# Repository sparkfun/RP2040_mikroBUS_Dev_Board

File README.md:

SparkFun RP2040 mikroBUS™ Development Board
========================================

[*SparkFun RP2040 mikroBUS™ Development Board (DEV-18721)*](https://www.sparkfun.com/products/18721)

The SparkFun RP2040 mikroBUS™ development board is a low-cost, high performance board with flexible digital interfaces featuring the Raspberry Pi Foundation's RP2040 microcontroller. Besides the Thing Plus or *Feather* footprint (with 18 GPIO pins), the board also includes an SD card slot, 16MB (128Mbit) flash memory, a JST single cell battery connector (with a charging circuit and fuel gauge sensor), an addressable WS2812 RGB LED, JTAG PTH pins, a mikroBUS™ socket, and our signature Qwiic connector.

_The RP2040 is supported with both C/C++ and MicroPython cross-platform development environments, including easy access to runtime debugging. It has UF2 boot and floating-point routines baked into the chip. While the chip has a large amount of internal RAM, the board includes an additional 16MB of external QSPI flash memory to store program code._

_The [mikroBUS™ standard](https://www.mikroe.com/mikrobus) was developed by [MikroElektronika](https://www.mikroe.com/). Similar to our [Qwiic](https://www.sparkfun.com/qwiic) and [MicroMod](https://www.sparkfun.com/micromod) interfaces, mikroBUS™ provides a standardized connection for add-on [Click boards™](https://www.mikroe.com/click-boards) to be hooked up to a microcontroller based development board._

Repository Contents
-------------------

* **/Documentation** - Data sheets, additional product information
* **/Hardware** - Eagle design files (.brd, .sch)

Documentation
--------------

* **[Hookup Guide](https://learn.sparkfun.com/tutorials/2004)** - SparkFun RP2040 mikroBUS™ Development Board
* **[Raspberry Pi RP2040 Datasheet](https://datasheets.raspberrypi.org/rp2040/rp2040_datasheet.pdf)** - Datasheet for the RP2040
* **[SparkFun Graphical Datasheets](https://github.com/sparkfun/Graphical_Datasheets)** - Graphical datasheets for various SparkFun products.

Product Versions
----------------
* [DEV-18721](https://www.sparkfun.com/products/18721) -  initial release

License Information
-------------------

This product is _**open source**_! 

Please review the LICENSE.md file for license information. 

If you have any questions or concerns on licensing, please contact technical support on our [SparkFun forums](https://forum.sparkfun.com/viewforum.php?f=152).

Distributed as-is; no warranty is given.

- Your friends at SparkFun.

_<COLLABORATION CREDIT>_

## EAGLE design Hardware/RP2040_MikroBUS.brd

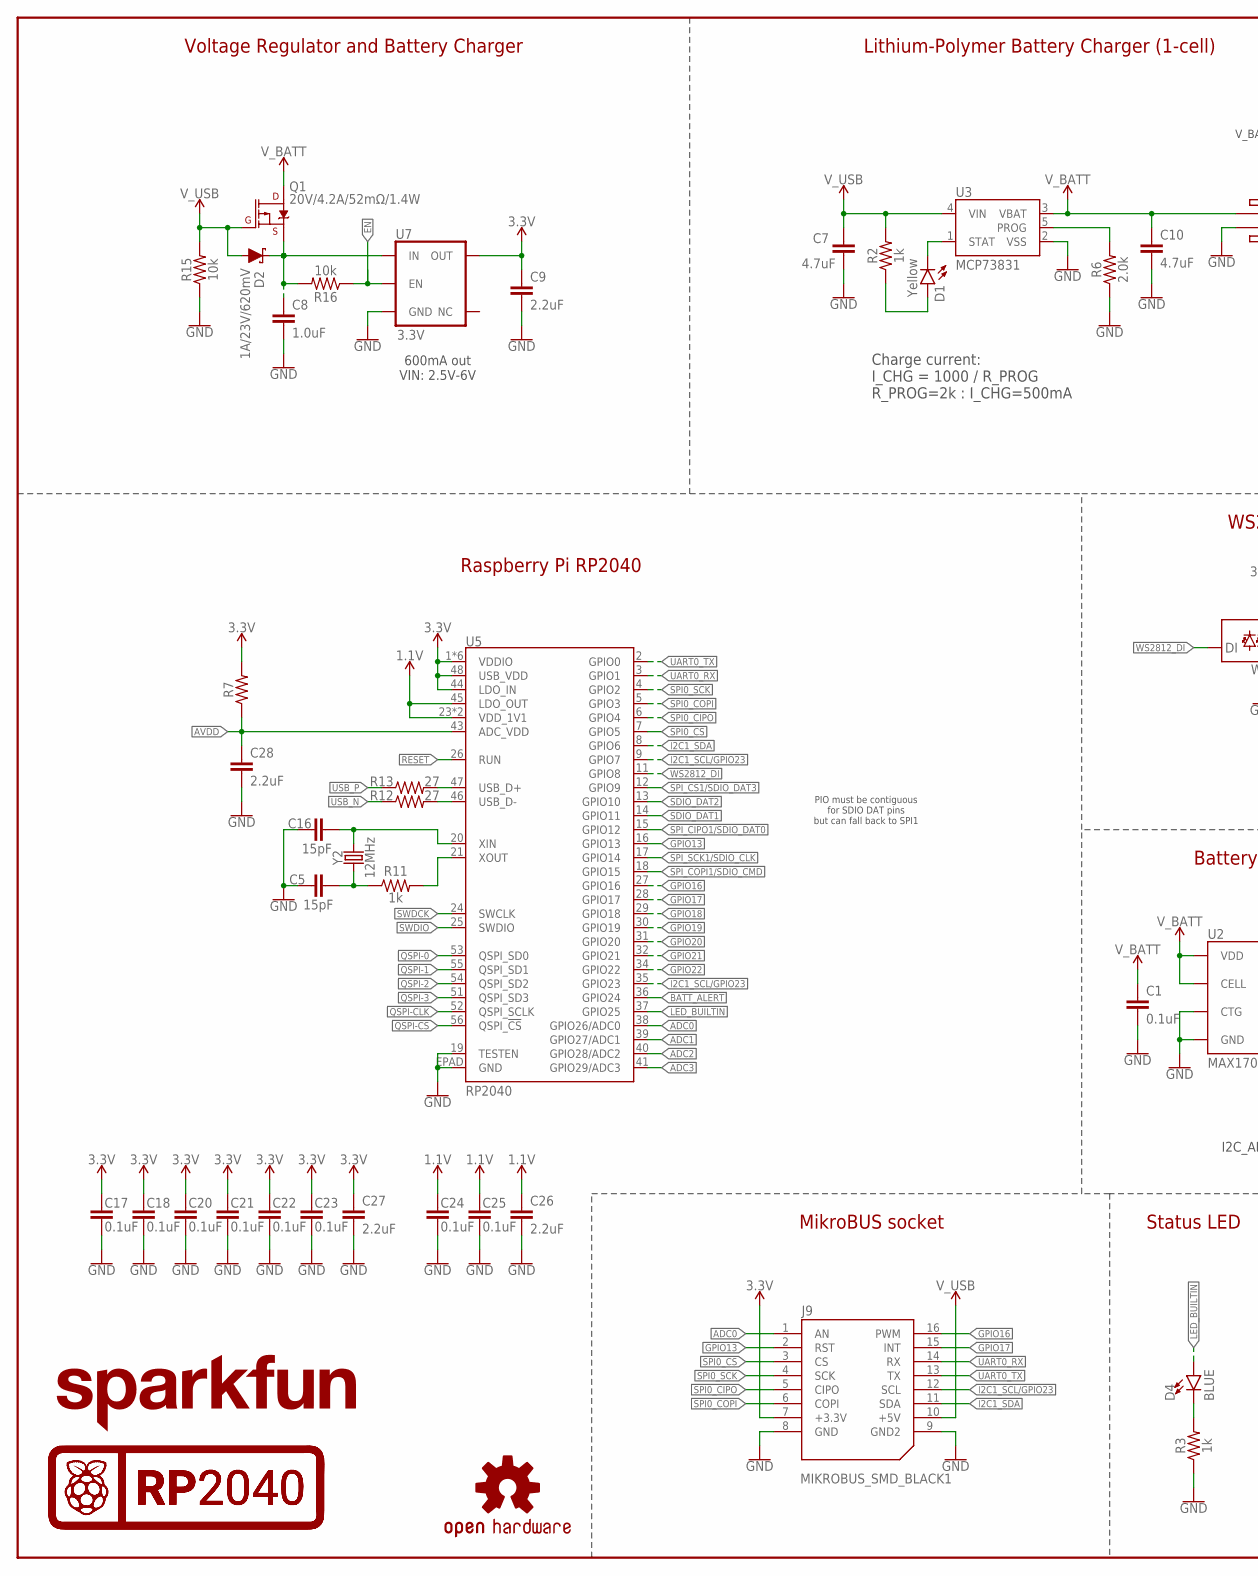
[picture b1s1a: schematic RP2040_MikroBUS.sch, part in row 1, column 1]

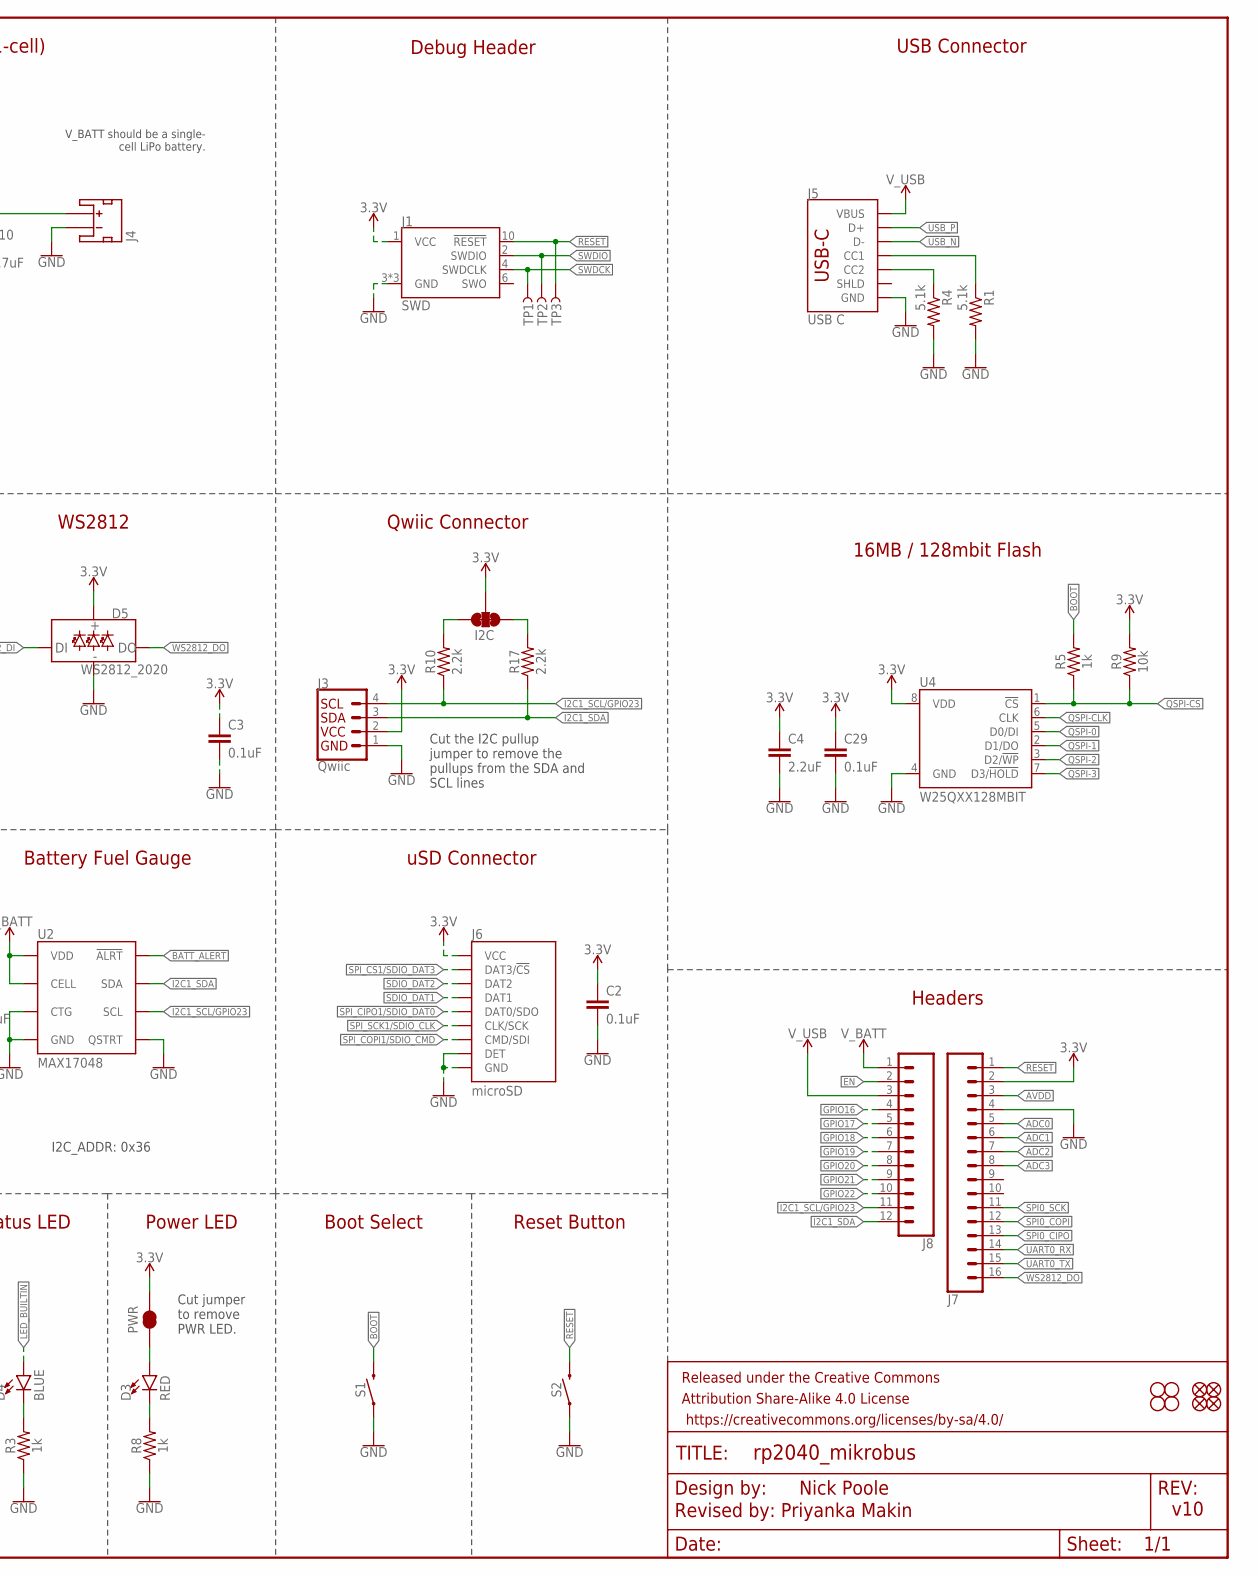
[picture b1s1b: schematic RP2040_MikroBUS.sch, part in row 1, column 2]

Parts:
C1, C2, C3, C17, C18, C20, C21, C22, C23, C24, C25, C29: 0.1uF; 0402-TIGHT
C4, C9, C26, C27, C28: 2.2uF; 0402-TIGHT
C5, C16: 15pF; 0402-TIGHT
C7, C10: 4.7uF; 0402-TIGHT
C8: 1.0uF; 0402-TIGHT
D1: Yellow; LED-0603
D2: 1A/23V/620mV; SOD-323
D3: RED; LED-0603
D4: BLUE; LED-0603
D5: WS2812_2020; WS2812-2020
FD1, FD2, FD3, FD4: FIDUCIALUFIDUCIAL; FIDUCIAL-MICRO
FRAME1: FRAME-LEDGER; CREATIVE_COMMONS
H1, H2, H3, H4: STAND-OFF
I2C: JUMPER-SMT_3_2-NC_TRACE_SILK; SMT-JUMPER_3_2-NC_TRACE_SILK
J1: SWD; 2X5-PTH-1.27MM
J3: Qwiic; JST04_1MM_RA
J4: JST_2MM_MALE; JST-2-SMD
J5: USB C; USB-C-16P-4LAYER-ISOLATED
J6: microSD; MICROSD-EXTERNALPIN
J7: CONN_161X16_NO_SILK; 1X16_NO_SILK
J8: CONN_12NO_SILK; 1X12_NO_SILK
J9: MIKROBUS_SMD_BLACK1; MIKROBUS_SMD_BLACK
LOGO1: OSHW-LOGOS; OSHW-LOGO-S
LOGO2: SFE_LOGO_NAME.1_INCH; SFE_LOGO_NAME_.1
PWR: JUMPER-SMT_2_NC_TRACE_SILK; SMT-JUMPER_2_NC_TRACE_SILK
Q1: 20V/4.2A/52mΩ/1.4W; SOT23-3
R1, R4: 5.1k; 0402-TIGHT
R2, R3, R5, R8, R11: 1k; 0402-TIGHT
R6: 2.0k; 0603
R7: 200OHM-0402T-1/16W-1%; 0402-TIGHT
R9, R15, R16: 10k; 0402-TIGHT
R10, R17: 2.2k; 0402-TIGHT
R12, R13: 27; 0402-TIGHT
S1, S2: MOMENTARY-SWITCH-SPST-SMD-5.2MM-TALL; TACTILE_SWITCH_SMD_5.2MM
TP1, TP2, TP3: TEST-POINT3X4; PAD.03X.04
U2: MAX17048; DFN-8
U3: MCP73831; SOT23-5
U4: W25QXX128MBIT; WSON-8-6X5-SKINNY_CENTERPAD
U5: RP2040; QFN-56
U7: 3.3V; SOT23-5
U$17, U$73: RASPI_RP2040_LOGO_10MM
Y2: 12MHz; CRYSTAL-SMD-2X2.5MM

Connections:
1.1V: C24.1, C25.1, C26.1, U5.23 (VDD_1V1), U5.45 (LDO_OUT), U5.50 (VDD_1V1)
3.3V: C2.1, C3.1, C4.1, C9.1, C17.1, C18.1, C20.1, C21.1, C22.1, C23.1, C27.1, C29.1, D5.VCC, I2C.2, J1.1 (VCC), J3.2, J6.4 (VCC), J7.2, J9.7 (+3.3V), PWR.2, R7.2, R9.2, U4.8 (VDD), U5.1 (VDDIO), U5.10 (VDDIO), U5.22 (VDDIO), U5.33 (VDDIO), U5.42 (VDDIO), U5.44 (LDO_IN), U5.48 (USB_VDD), U5.49 (VDDIO), U7.5 (OUT)
!BATT_ALERT!: U2.5 (!ALRT), U5.36 (GPIO24)
!BOOT!: R5.2, S1.3 (2)
!QSPI-CS!: R5.1, R9.1, U4.1 (!CS!), U5.56 (QSPI_!CS!)
!RESET!: J1.10 (!RESET), J7.1, S2.3 (2), TP3.1, U5.26 (RUN)
!SPI0_CS!: J9.3 (CS), U5.7 (GPIO5)
ADC0: J7.5, J9.1 (AN), U5.38 (GPIO26/ADC0)
ADC1: J7.6, U5.39 (GPIO27/ADC1)
ADC2: J7.7, U5.40 (GPIO28/ADC2)
ADC3: J7.8, U5.41 (GPIO29/ADC3)
AVDD: C28.1, J7.3, R7.1, U5.43 (ADC_VDD)
EN: J8.2, R16.1, U7.3 (EN)
GND: C1.2, C2.2, C3.2, C4.2, C5.1, C7.2, C8.2, C9.2, C10.2, C16.1, C17.2, C18.2, C20.2, C21.2, C22.2, C23.2, C24.2, C25.2, C26.2, C27.2, C28.2, C29.2, D5.GND, J1.3 (GND), J1.5 (GND), J1.9 (GND), J3.1, J4.1 (-), J5.GND, J5.GND2 (GND), J6.6 (GND), J6.9 (DET), J6.10 (GND), J6.11 (GND), J6.12 (GND), J6.13 (GND), J7.4, J9.8 (GND), J9.9 (GND2), R1.2, R3.1, R4.2, R6.1, R8.1, R15.1, S1.1, S2.1, U2.1 (CTG), U2.4 (GND), U2.6 (QSTRT), U2.9 (GND), U3.2 (VSS), U4.4 (GND), U5.19 (TESTEN), U5.EPAD (GND), U7.2 (GND)
GPIO13: J9.2 (RST), U5.16 (GPIO13)
GPIO16: J8.4, J9.16 (PWM), U5.27 (GPIO16)
GPIO17: J8.5, J9.15 (INT), U5.28 (GPIO17)
GPIO18: J8.6, U5.29 (GPIO18)
GPIO19: J8.7, U5.30 (GPIO19)
GPIO20: J8.8, U5.31 (GPIO20)
GPIO21: J8.9, U5.32 (GPIO21)
GPIO22: J8.10, U5.34 (GPIO22)
I2C1_SCL/GPIO23: J3.4, J8.11, J9.12 (SCL), R10.1, U2.7 (SCL), U5.9 (GPIO7), U5.35 (GPIO23)
I2C1_SDA: J3.3, J8.12, J9.11 (SDA), R17.1, U2.8 (SDA), U5.8 (GPIO6)
LED_BUILTIN: D4.A, U5.37 (GPIO25)
unnamed: D4.C, R3.2
unnamed: I2C.3, R10.2
unnamed: I2C.1, R17.2
unnamed: R11.2, U5.21 (XOUT)
unnamed: C16.2, U5.20 (XIN), Y2.P3 (2)
unnamed: C5.2, R11.1, Y2.P1 (1)
unnamed: D3.C, R8.2
unnamed: D1.C, U3.1 (STAT)
unnamed: D3.A, PWR.1
unnamed: J5.A5 (CC1), R1.1
unnamed: J5.B5 (CC2), R4.1
unnamed: R6.2, U3.5 (PROG)
unnamed: C8.1, D2.C, Q1.2 (S), R16.2, U7.1 (IN)
unnamed: D1.A, R2.1
QSPI-0: U4.5 (D0/DI), U5.53 (QSPI_SD0)
QSPI-1: U4.2 (D1/DO), U5.55 (QSPI_SD1)
QSPI-2: U4.3 (D2/!WP!), U5.54 (QSPI_SD2)
QSPI-3: U4.7 (D3/!HOLD!), U5.51 (QSPI_SD3)
QSPI-CLK: U4.6 (CLK), U5.52 (QSPI_SCLK)
SDIO_DAT1: J6.8 (DAT1), U5.14 (GPIO11)
SDIO_DAT2: J6.1 (DAT2), U5.13 (GPIO10)
SPI0_CIPO: J7.13, J9.5 (CIPO), U5.6 (GPIO4)
SPI0_COPI: J7.12, J9.6 (COPI), U5.5 (GPIO3)
SPI0_SCK: J7.11, J9.4 (SCK), U5.4 (GPIO2)
SPI_!CS1!/SDIO_DAT3: J6.2 (DAT3/!CS!), U5.12 (GPIO9)
SPI_CIPO1/SDIO_DAT0: J6.7 (DAT0/SDO), U5.15 (GPIO12)
SPI_COPI1/SDIO_CMD: J6.3 (CMD/SDI), U5.18 (GPIO15)
SPI_SCK1/SDIO_CLK: J6.5 (CLK/SCK), U5.17 (GPIO14)
SWDCK: J1.4 (SWDCLK), TP1.1, U5.24 (SWCLK)
SWDIO: J1.2 (SWDIO), TP2.1, U5.25 (SWDIO)
UART0_RX: J7.14, J9.14 (RX), U5.3 (GPIO1)
UART0_TX: J7.15, J9.13 (TX), U5.2 (GPIO0)
USB_F_N: R12.2, U5.46 (USB_D-)
USB_F_P: R13.2, U5.47 (USB_D+)
USB_N: J5.A7 (D-), J5.B7 (D-), R12.1
USB_P: J5.A6 (D+), J5.B6 (D+), R13.1
V_BATT: C1.1, C10.1, J4.2 (+), J8.1, Q1.3 (D), U2.2 (CELL), U2.3 (VDD), U3.3 (VBAT)
V_USB: C7.1, D2.A, J5.VBUS1 (VBUS), J5.VBUS2 (VBUS), J8.3, J9.10 (+5V), Q1.1 (G), R2.2, R15.2, U3.4 (VIN)
WS2812_DI: D5.DI, U5.11 (GPIO8)
WS2812_DO: D5.DO, J7.16

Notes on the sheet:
V_BATT should be a single- cell LiPo battery.
Charge current: I_CHG = 1000 / R_PROG R_PROG=2k : I_CHG=500mA
Voltage Regulator and Battery Charger
Lithium-Polymer Battery Charger (1-cell)
600mA out VIN: 2.5V-6V
Reset Button
Status LED
Headers
v10
Qwiic Connector
USB Connector
Cut the I2C pullup jumper to remove the pullups from the SDA and SCL lines
Raspberry Pi RP2040
PIO must be contiguous for SDIO DAT pins but can fall back to SPI1
16MB / 128mbit Flash
uSD Connector
Battery Fuel Gauge
WS2812
I2C_ADDR: 0x36
Boot Select
Debug Header
Power LED
MikroBUS socket
Nick Poole
Revised by: Priyanka Makin
Cut jumper to remove PWR LED.

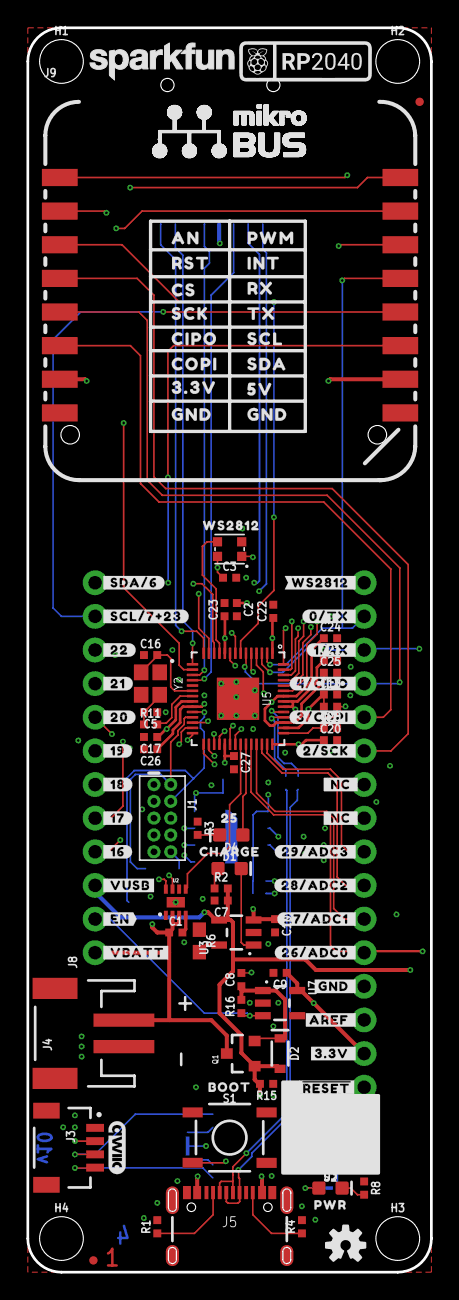
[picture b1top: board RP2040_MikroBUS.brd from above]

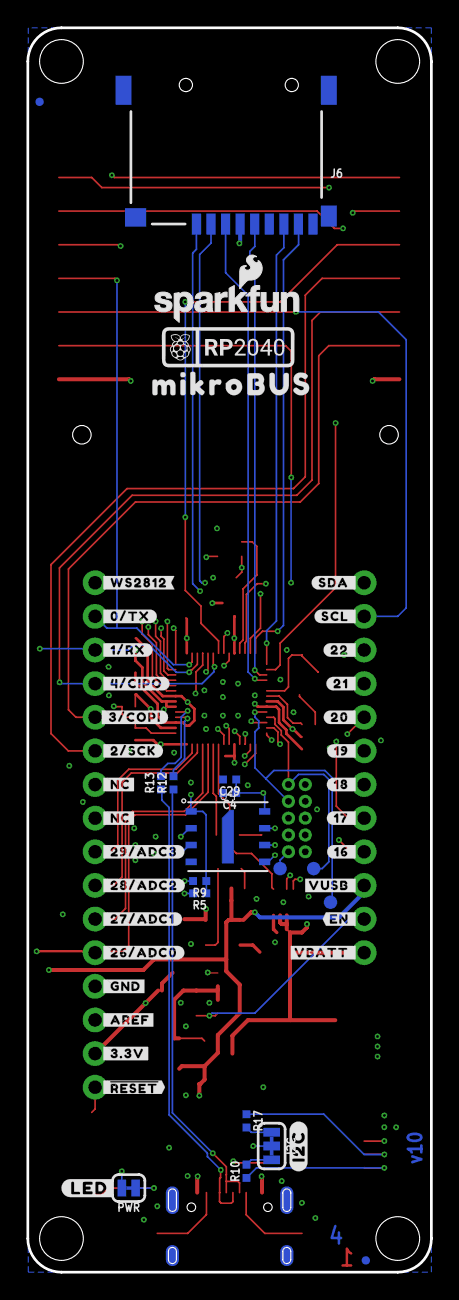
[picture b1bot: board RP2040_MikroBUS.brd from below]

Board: 4 copper layers, 30.5 x 94.0 mm, 161 parts (50 on the bottom side), 65 nets.

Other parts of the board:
U$1: #_16#0
U$2: #_17#0
U$3: #_18#0
U$4: #_19#0
U$5: #_20#0
U$6: #_21#0
U$7: #_22#0
U$8: #_SCL#7#23#0
U$9: #_SDA#6#0
U$10: #WS2812_#0
U$11: #0#TX_#0
U$12: #1#RX_#0
U$13: #4#CIPO_#0
U$14: #3#COPI_#0
U$15: #2#SCK_#0
U$16: PWR0
U$18: #29#ADC3_#0
U$19: #28#ADC2_#0
U$20: #27#ADC1_#0
U$21: #26#ADC0_#0
U$22: #_VUSB#0
U$23: #_EN#0
U$24: #_VBATT#0
U$25: #GND_#0
U$26: #AREF_#0
U$27: #3#3V_#0
U$28: ##RESET##0
U$29: AN0
U$30: WS28120
U$31: ORDERING_INSTRUCTIONS
U$32: SFE_LOGO_NAME_FLAME_.1
U$33: #SCL_#0
U$34: #SDA_#0
U$35: #_#RESET##0
U$36: #_3#3V#0
U$37: #_AREF#0
U$38: #_GND#0
U$39: #_26#ADC0#0
U$40: #_27#ADC1#0
U$41: #_28#ADC2#0
U$42: #_29#ADC3#0
U$43: #LED#0
U$44: RST0
U$45: CS0
U$47, U$48: #_NC_#0
U$49: #_2#SCK#0
U$50: #_3#COPI#0
U$51: #_4#CIPO#0
U$52: #_1#RX#0
U$53: #_0#TX#0
U$54: 250
U$55: CHARGE0
U$56: BOOT0
U$57: #22_#0
U$58: #21_#0
U$59: #20_#0
U$60: CIPO0
U$61: #19_#0
U$62: #18_#0
U$63: #17_#0
U$64: QWIIC_4MM
U$65: #16_#0
U$66: #VUSB_#0
U$67: #EN_#0
U$68: #VBATT_#0
U$69, U$70: #_NC#0
U$71: #_WS2812#0
U$72: #I2C#0
U$74: SCK0
U$75: COPI0
U$76: 3#3V0
U$77, U$78: GND0
U$79: 5V0
U$80: SDA0
U$81: SCL0
U$82: TX0
U$83: RX0
U$84: INT0
U$85: PWM0
U$88: MIKROBUS0

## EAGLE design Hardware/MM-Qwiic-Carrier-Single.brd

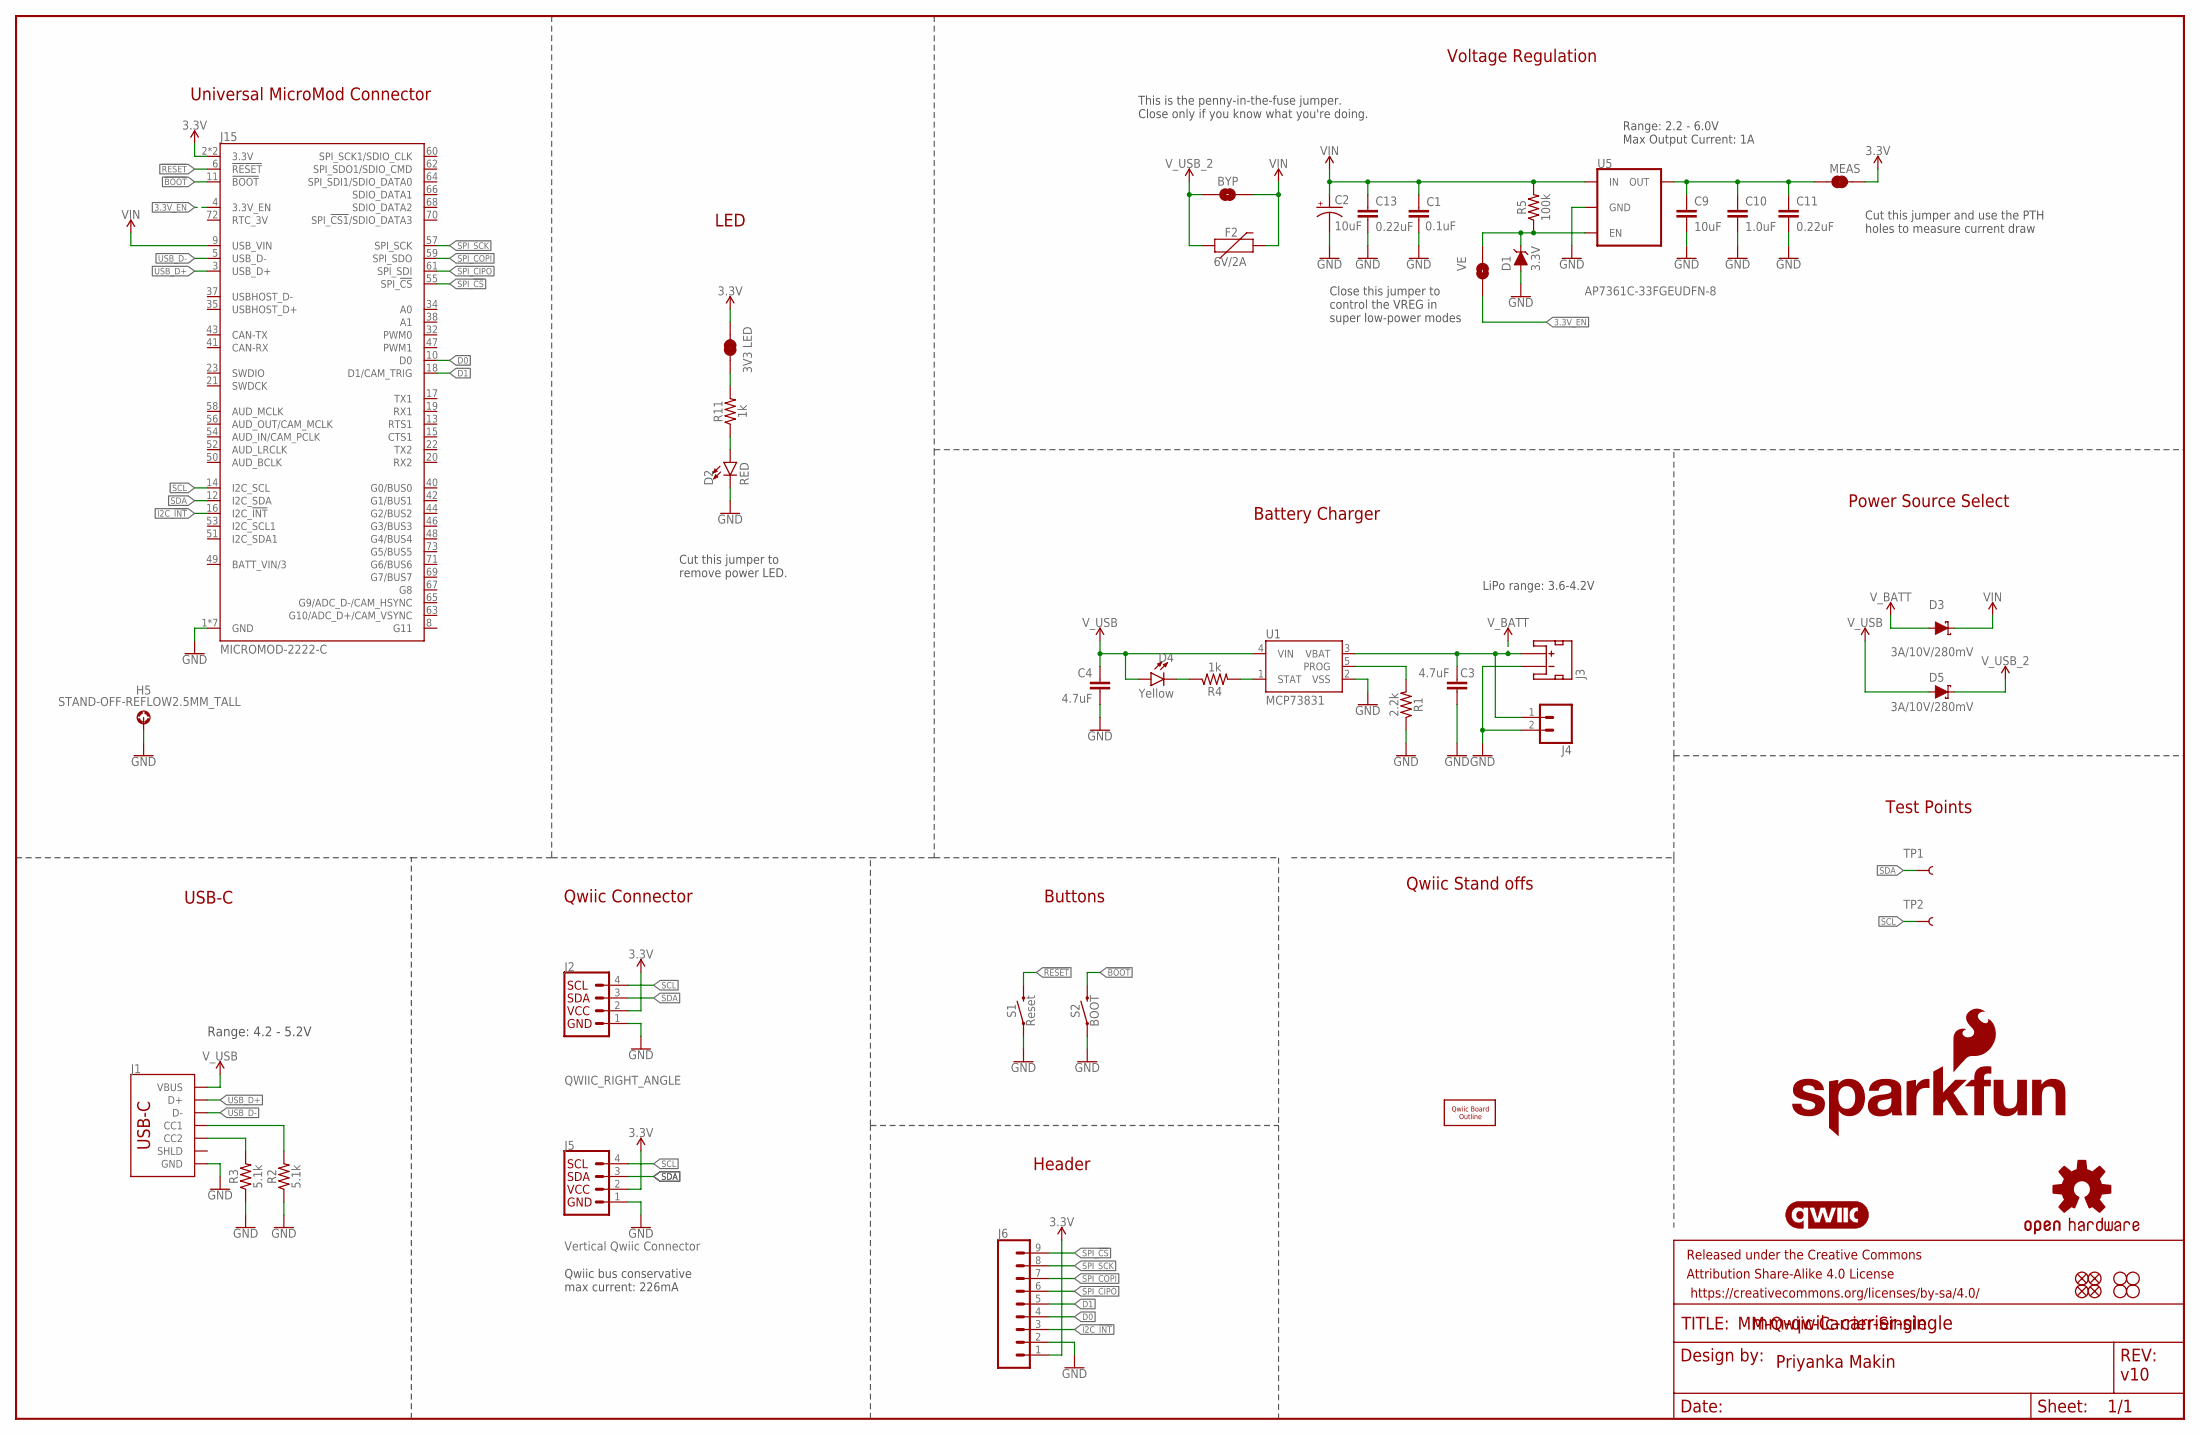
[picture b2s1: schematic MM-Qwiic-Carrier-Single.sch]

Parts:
BYP: JUMPER-SMT_2_NO_SILK; SMT-JUMPER_2_NO_SILK
C1: 0.1uF; 0603
C2: 10uF; EIA3216
C3, C4: 4.7uF; 0603
C9: 10uF; 0603
C10: 1.0uF; 0603
C11, C13: 0.22uF; 0603
D1: 3.3V; SOD-323
D2: RED; LED-0603
D3, D5: 3A/10V/280mV; SOD-323
D4: Yellow; LED-0603
F2: 6V/2A; 1210
FD1, FD2, FD3, FD4: FIDUCIALUFIDUCIAL; FIDUCIAL-MICRO
FRAME1: FRAME-LEDGER; CREATIVE_COMMONS
H1, H2, H3, H4: STAND-OFF
H5: STAND-OFF-REFLOW2.5MM_TALL; STAND-OFF-REFLOW-M2.5
J1: USB_C_2-LAYER_PADS; USB-C-16P-2LAYER-PADS
J2: QWIIC_RIGHT_ANGLE; JST04_1MM_RA
J3: JST_2MM_MALE; JST-2-SMD
J4: CONN_021X02_NO_SILK; 1X02_NO_SILK
J5: Vertical Qwiic Connector; JST04_1MM_VERT
J6: CONN_09NO_SILK; 1X09_NO_SILK
J15: MICROMOD-2222-C; M.2-CONNECTOR-E
JP4: 3V3 LED; SMT-JUMPER_2_NC_TRACE_SILK
JP6: VE; SMT-JUMPER_2_NO_SILK
LOGO1: SFE_LOGO_NAME_FLAME.2_INCH; SFE_LOGO_NAME_FLAME_.2
LOGO2: QWIIC_LOGO_CONNECTOR; QWIIC_5.5MM
LOGO3: OSHW-LOGOM; OSHW-LOGO-M
MEAS: JUMPER-COMBO_2_NC_TRACE; COMBO-JUMPER_2_NC_TRACE
R1: 2.2k; 0603
R2, R3: 5.1k; 0603
R4, R11: 1k; 0603
R5: 100k; 0603
S1: Reset; TACTILE_SWITCH_SMD_5.2MM
S2: BOOT; TACTILE_SWITCH_SMD_5.2MM
TP1, TP2: TEST-POINT3X5; PAD.03X.05
U1: MCP73831; SOT23-5
U5: AP7361C-33FGEUDFN-8; UDFN-8
U$5: QWIIC_BOARD_OUTLINESTANDOFF; QWIIC_BOARD_MOUNT_SMD_STANDOFFS

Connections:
3.3V: J2.2, J5.2, J6.1, J15.2 (3.3V), J15.74 (3.3V), JP4.2, MEAS.2, MEAS.4 (2)
3.3V_EN: J15.4 (3.3V_EN), JP6.1
!BOOT!: J15.11 (!BOOT!), S2.3 (2), S2.4 (2)
!RESET!: J15.6 (!RESET!), S1.3 (2), S1.4 (2)
D0: J6.4, J15.10 (D0)
D1: J6.5, J15.18 (D1/CAM_TRIG)
GND: C1.2, C2.-, C3.2, C4.2, C9.2, C10.2, C11.2, C13.2, D1.A, D2.C, H5.1, J1.GND, J1.GND2 (GND), J2.1, J3.1 (-), J4.2, J5.1, J6.2, J15.1 (GND), J15.7 (GND), J15.33 (GND), J15.36 (GND), J15.39 (GND), J15.45 (GND), J15.75 (GND), R1.1, R2.1, R3.1, S1.1, S1.2 (1), S2.1, S2.2 (1), U1.2 (VSS), U5.4 (GND), U5.EP (GND)
I2C_!INT!: J6.3, J15.16 (I2C_!INT!)
unnamed: C9.1, C10.1, C11.1, MEAS.1, MEAS.3 (1), U5.1 (OUT)
unnamed: R1.2, U1.5 (PROG)
unnamed: D4.C, R4.1
unnamed: JP4.1, R11.2
unnamed: D2.A, R11.1
unnamed: R4.2, U1.1 (STAT)
unnamed: J1.A5 (CC1), R2.2
unnamed: J1.B5 (CC2), R3.2
SCL: J2.4, J5.4, J15.14 (I2C_SCL), TP2.P$1
SDA: J2.3, J5.3, J15.12 (I2C_SDA), TP1.P$1
SPI_!CS!: J6.9, J15.55 (SPI_!CS!)
SPI_CIPO: J6.6, J15.61 (SPI_SDI)
SPI_COPI: J6.7, J15.59 (SPI_SDO)
SPI_SCK: J6.8, J15.57 (SPI_SCK)
USB_D+: J1.A6 (D+), J1.B6 (D+), J15.3 (USB_D+)
USB_D-: J1.A7 (D-), J1.B7 (D-), J15.5 (USB_D-)
VIN: BYP.2, C1.1, C2.+, C13.1, D3.C, F2.2, J15.9 (USB_VIN), R5.2, U5.8 (IN)
VREG_EN: D1.C, JP6.2, R5.1, U5.5 (EN)
V_BATT: C3.1, D3.A, J3.2 (+), J4.1, U1.3 (VBAT)
V_USB: C4.1, D4.A, D5.A, J1.VBUS1 (VBUS), J1.VBUS2 (VBUS), U1.4 (VIN)
V_USB_2: BYP.1, D5.C, F2.1

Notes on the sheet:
USB-C
Universal MicroMod Connector
Priyanka Makin
MM-Qwiic-Carrier-Single
LED
v10
Cut this jumper to remove power LED.
Range: 4.2 - 5.2V
Voltage Regulation
Range: 2.2 - 6.0V Max Output Current: 1A
Close this jumper to control the VREG in super low-power modes
This is the penny-in-the-fuse jumper. Close only if you know what you're doing.
Qwiic Connector
Buttons
Battery Charger
Qwiic Stand offs
Power Source Select
Test Points
Qwiic bus conservative max current: 226mA
Header
Cut this jumper and use the PTH holes to measure current draw
LiPo range: 3.6-4.2V

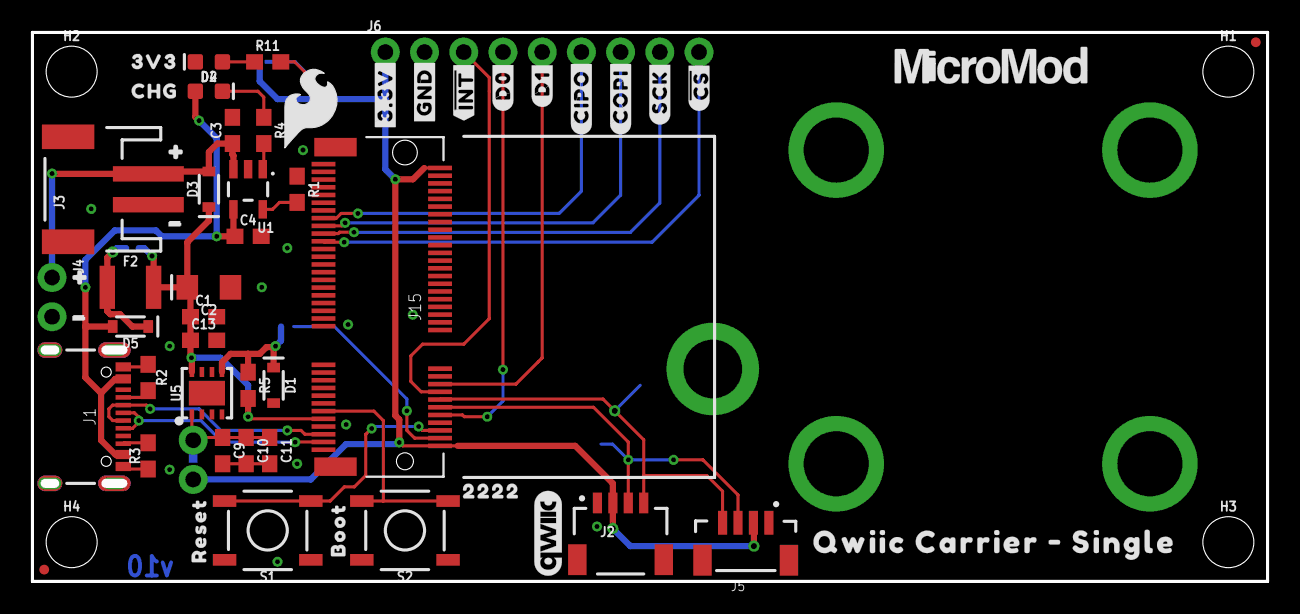
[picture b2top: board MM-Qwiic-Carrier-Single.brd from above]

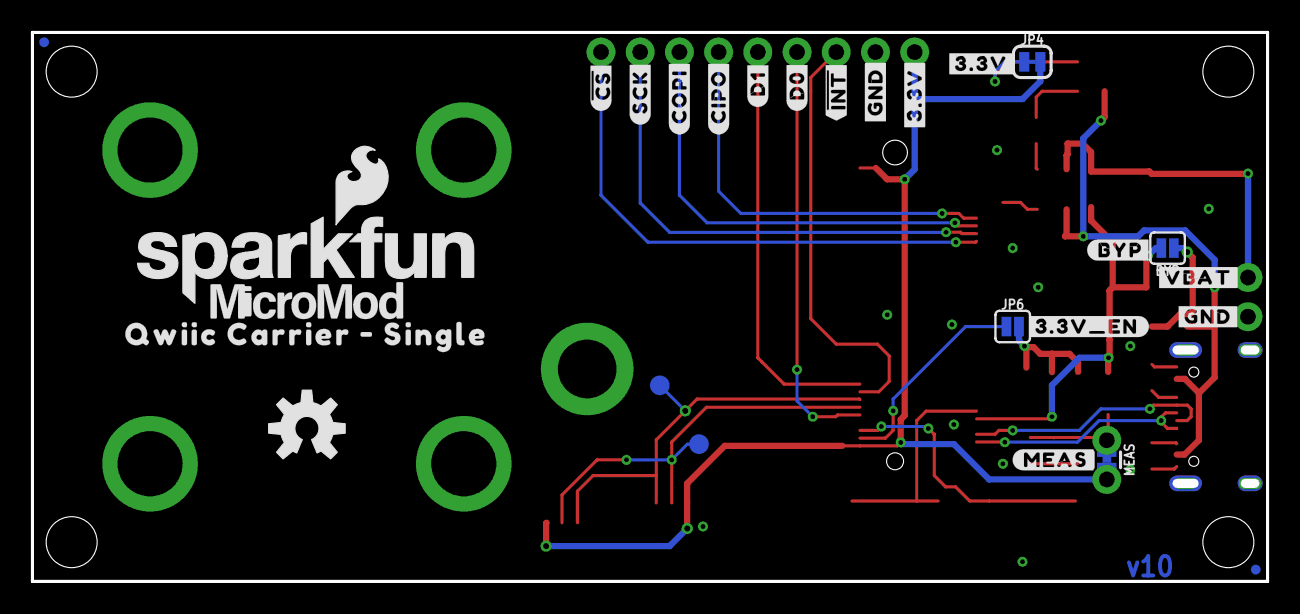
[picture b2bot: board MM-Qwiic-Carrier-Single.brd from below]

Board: 2 copper layers, 80.0 x 35.6 mm, 89 parts (27 on the bottom side), 29 nets.

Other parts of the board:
U$1: #3#3V_EN#0
U$2, U$19: QWIIC_CARRIER_#_SINGLE0
U$3: 3V30
U$4: CHG0
U$6, U$35, U$38: #3#3V#0
U$7: #BYP#0
U$8, U$14, U$33: #GND#0
U$9: #MEAS#0
U$11, U$32, U$36, U$37: #0
U$12: #VBAT#0
U$15, U$16: ##INT##0
U$17, U$18: #D0#0
U$20, U$21: #D1#0
U$22, U$23: #CIPO#0
U$24, U$25: #COPI#0
U$26, U$27: #SCK#0
U$28, U$29: ##CS##0
U$30: RESET0
U$31: BOOT0
U$34: 22220
U$44: SFE_LOGO_FLAME_.2
U$67, U$68: MICROMOD_LOGO_.5

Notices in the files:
parts and their libraries:
SparkFun-Aesthetics: Licensing: Creative Commons ShareAlike 4.0 International - https://creativecommons.org/licenses/by-sa/4.0
SparkFun-Aesthetics: Released under the Creative Commons Attribution Share-Alike 4.0 License
SparkFun-Aesthetics: https://creativecommons.org/licenses/by-sa/4.0
